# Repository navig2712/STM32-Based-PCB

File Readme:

This is the schematic and PCB design based on stm32F4 mcu.
its a breakout board.
Designed in KiCAD

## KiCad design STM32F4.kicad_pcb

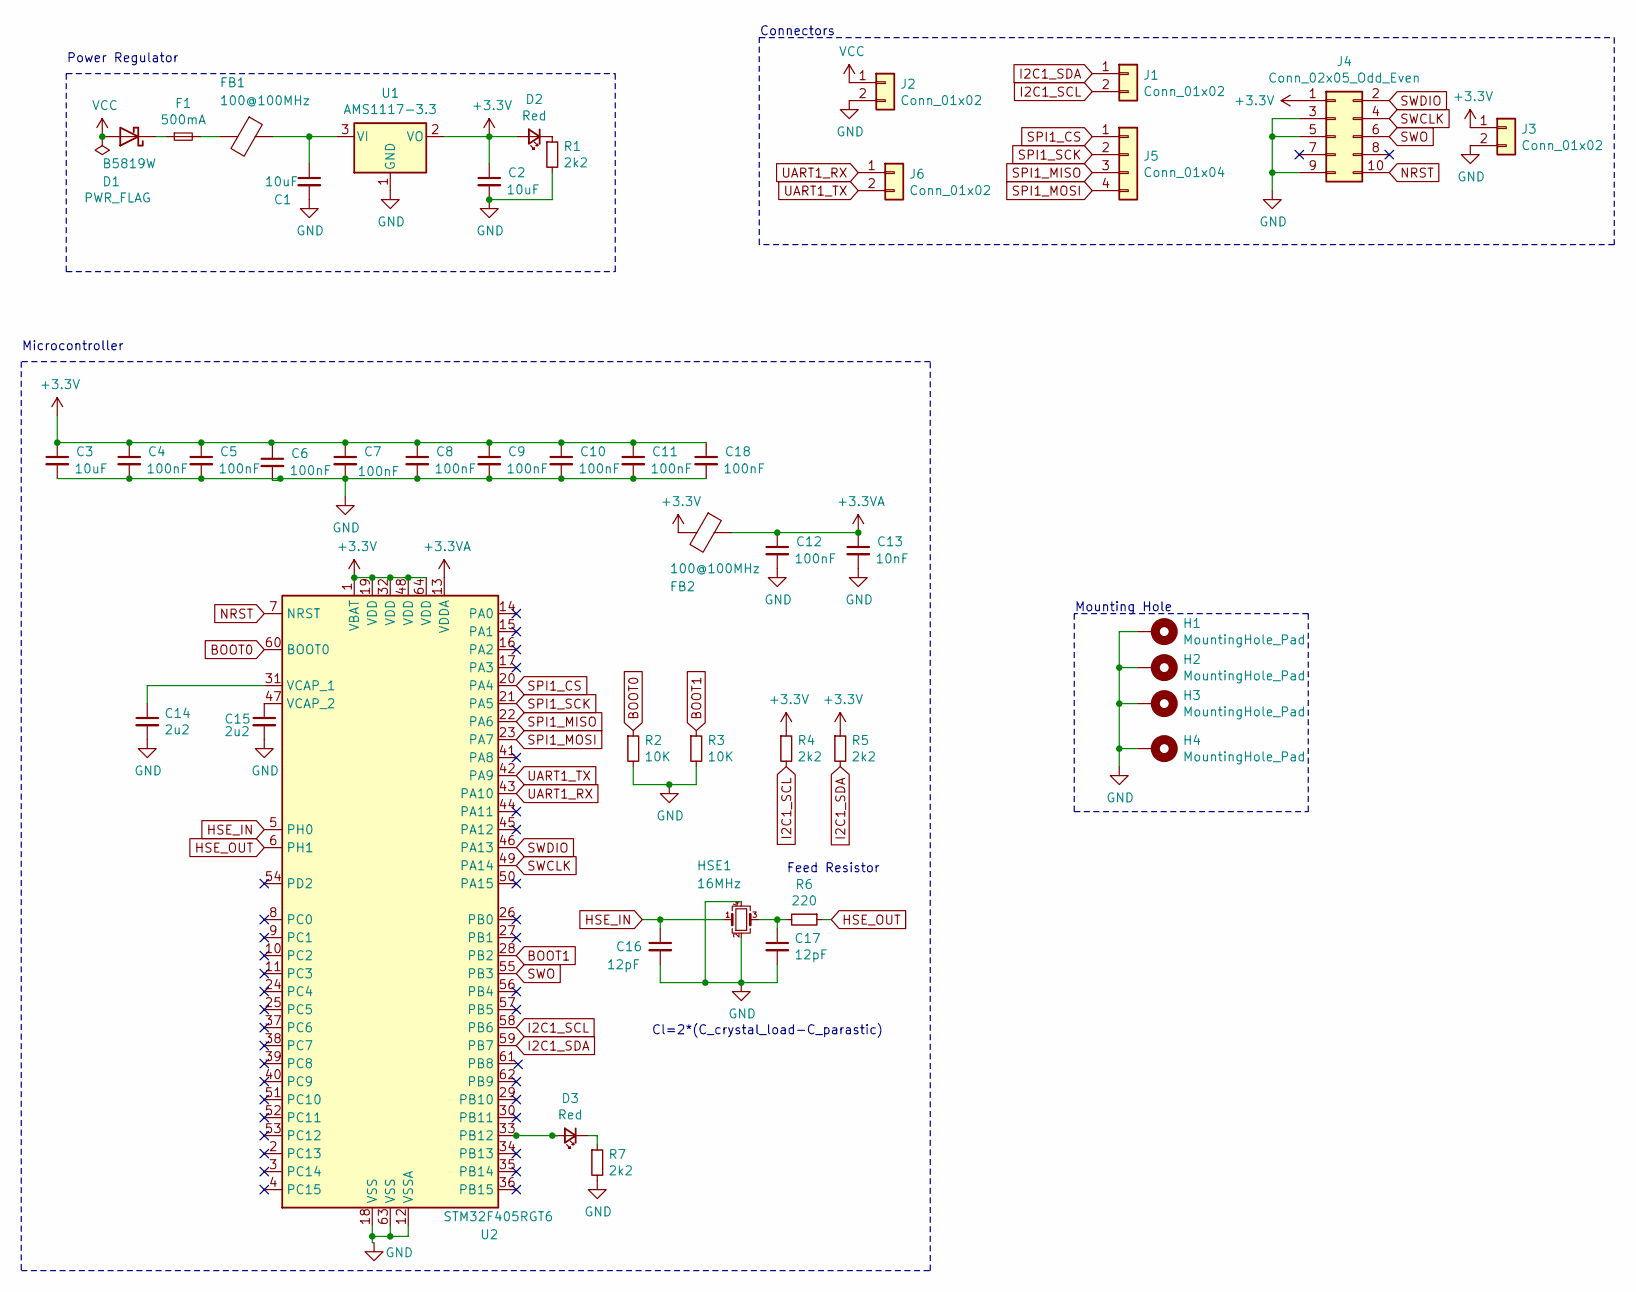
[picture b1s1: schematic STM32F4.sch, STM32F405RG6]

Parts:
C1, C2: 10uF; C_0805_2012Metric
C3: 10uF; C_0603_1608Metric
C4, C5, C6, C7, C8, C9, C10, C11, C12, C18: 100nF; C_0402_1005Metric
C13: 10nF; C_0402_1005Metric
C14, C15: 2u2; C_0603_1608Metric
C16, C17: 12pF; C_0402_1005Metric
D1: B5819W; D_SOD-123
D2, D3: Red; LED_0603_1608Metric
F1: 500mA; Fuse_0603_1608Metric
FB1, FB2: 100@100MHz; L_0805_2012Metric
H1, H2, H3, H4: MountingHole_Pad; MountingHole_4.3mm_M4_Pad_Via
HSE1: 16MHz; Crystal_SMD_3225-4Pin_3.2x2.5mm
J1, J2, J3, J6: Conn_01x02; PinHeader_1x02_P2.54mm_Vertical
J4: Conn_02x05_Odd_Even; PinHeader_2x05_P1.27mm_Vertical_SMD
J5: Conn_01x04; PinHeader_1x04_P2.54mm_Vertical
R1, R7: 2k2; R_0201_0603Metric
R2, R3: 10K; R_0402_1005Metric
R4, R5: 2k2; R_0402_1005Metric
R6: 220; R_0402_1005Metric
U1: AMS1117-3.3; SOT-223-3_TabPin2
U2: STM32F405RGT6; LQFP-64_10x10mm_P0.5mm

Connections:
+3.3VA: C12.1, C13.1, FB2.1, U2.13 (VDDA)
+3V3: C2.1, C3.1, C4.1, C5.1, C6.1, C7.1, C8.1, C9.1, C10.1, C11.1, C18.1, D2.2 (A), FB2.2, J3.1, J4.1, R4.1, R5.1, U1.2 (VO), U2.1 (VBAT), U2.19 (VDD), U2.32 (VDD), U2.48 (VDD), U2.64 (VDD); also elsewhere on the board
BOOT0: R2.1, U2.60 (BOOT0)
BOOT1: R3.1, U2.28 (PB2)
GND: C1.2, C2.2, C3.2, C4.2, C5.2, C6.2, C7.2, C8.2, C9.2, C10.2, C11.2, C12.2, C13.2, C14.2, C15.2, C16.2, C17.2, C18.2, H1.1, H2.1, H3.1, H4.1, HSE1.2, HSE1.4, J2.2, J3.2, J4.3, J4.5, J4.9, R1.2, R2.2, R3.2, R7.2, U1.1 (GND), U2.12 (VSSA), U2.18 (VSS), U2.63 (VSS); also elsewhere on the board
HSE_IN: C16.1, HSE1.1, U2.5 (PH0)
HSE_OUT: R6.1, U2.6 (PH1)
I2C1_SCL: J1.2, R4.2, U2.58 (PB6)
I2C1_SDA: J1.1, R5.2, U2.59 (PB7)
NRST: J4.10, U2.7 (NRST); also elsewhere on the board
unnamed: C1.1, FB1.1, U1.3 (VI)
unnamed: C14.1, U2.31 (VCAP_1)
unnamed: C15.1, U2.47 (VCAP_2)
unnamed: C17.1, HSE1.3, R6.2
unnamed: D1.1 (K), F1.1
unnamed: D2.1 (K), R1.1
unnamed: D3.1 (K), R7.1
unnamed: D3.2 (A), U2.33 (PB12)
unnamed: F1.2, FB1.2
SPI1_CS: J5.1, U2.20 (PA4)
SPI1_MISO: J5.3, U2.22 (PA6)
SPI1_MOSI: J5.4, U2.23 (PA7)
SPI1_SCK: J5.2, U2.21 (PA5)
SWCLK: J4.4, U2.49 (PA14); also elsewhere on the board
SWDIO: J4.2, U2.46 (PA13); also elsewhere on the board
SWO: J4.6, U2.55 (PB3); also elsewhere on the board
UART1_RX: J6.1, U2.43 (PA10)
UART1_TX: J6.2, U2.42 (PA9)
VCC: D1.2 (A), J2.1

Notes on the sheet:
Power Regulator
Cl=2*(C_crystal_load-C_parastic)
Feed Resistor
Microcontroller
Connectors
Mounting Hole

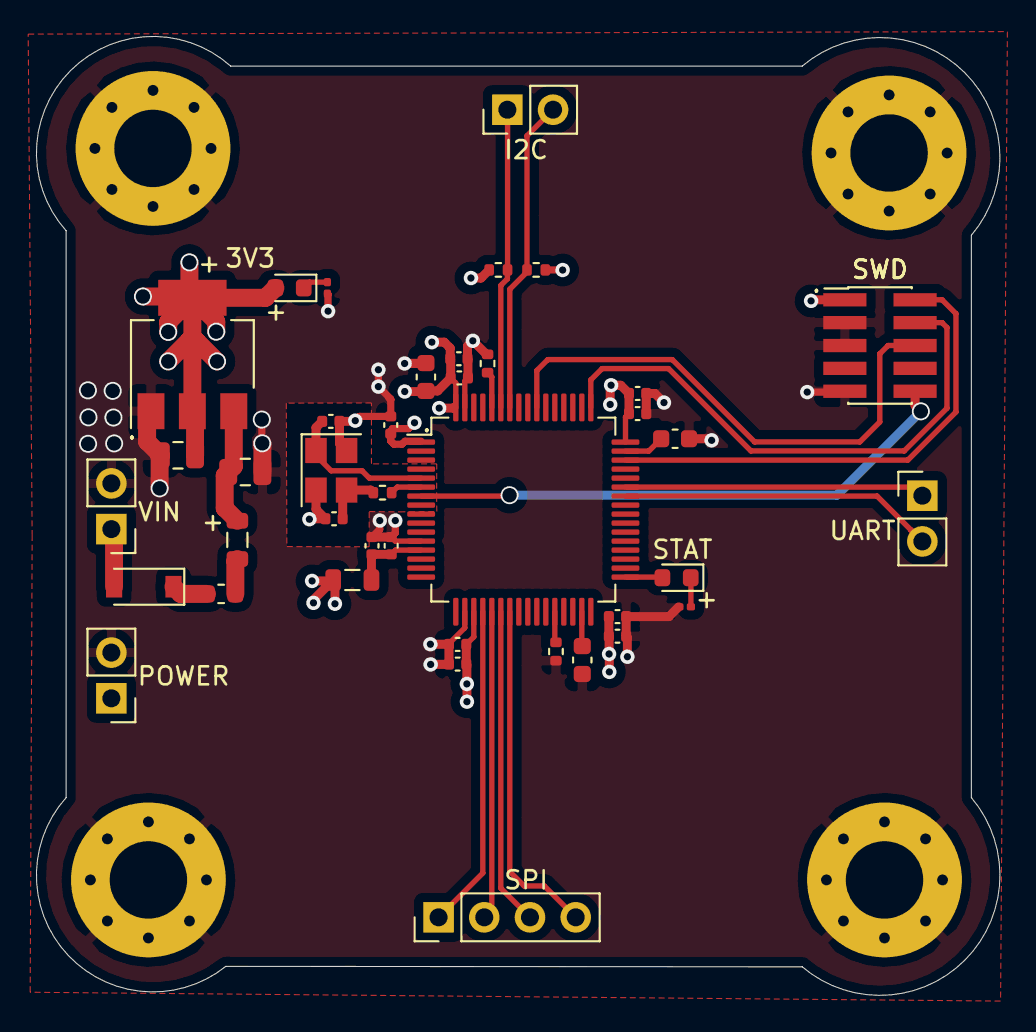
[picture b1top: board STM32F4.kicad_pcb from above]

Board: 4 copper layers, 53.5 x 53.3 mm, 44 parts (0 on the bottom side), 29 nets.

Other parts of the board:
SWD: Conn_02x05_Odd_Even; PinHeader_2x05_P1.27mm_Vertical_SMD

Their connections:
+3V3: SWD.1; also elsewhere on the board
GND: SWD.3, SWD.5, SWD.9; also elsewhere on the board
NRST: SWD.10; also elsewhere on the board
SWCLK: SWD.4; also elsewhere on the board
SWDIO: SWD.2; also elsewhere on the board
SWO: SWD.6; also elsewhere on the board

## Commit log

2022-02-28 Rename Readme to Readme.md
